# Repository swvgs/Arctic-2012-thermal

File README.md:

Arctic-2012-thermal
===================
This is Andrew Vaccaro's thermal processing script that was made to work with
raw data from Therma.

As of 5/2/13, these scripts are in a preliminary stage. They are only run from
the command line and require Python 2 to be installed. Later versions will
"hopefully" be stand-alone and have a GUI (assuming I ever get to them).

tim2.py takes original data files and splits them into multiple files, each one
containing the data along one survey line. tim2.py takes the data files and
processes them down to an equivalent number of data points between each survey
marker.

Currently, an unknown error prevents all of the code from being run in the same
file. Not entirely sure why, but splitting into two files works (thanks, CJ).
That being said, all file names and numbers are hard-coded into the scripts.
Annoying, but it's fairly simple to go in and edit the file name in tim2.py and
then the number of files produced in tim2.py.

tim3.py is in the works. It should be a single file that does the work of tim.py
and tim2.py. It is planned to account for error exceptions as well as gaps in or
issues with the data.

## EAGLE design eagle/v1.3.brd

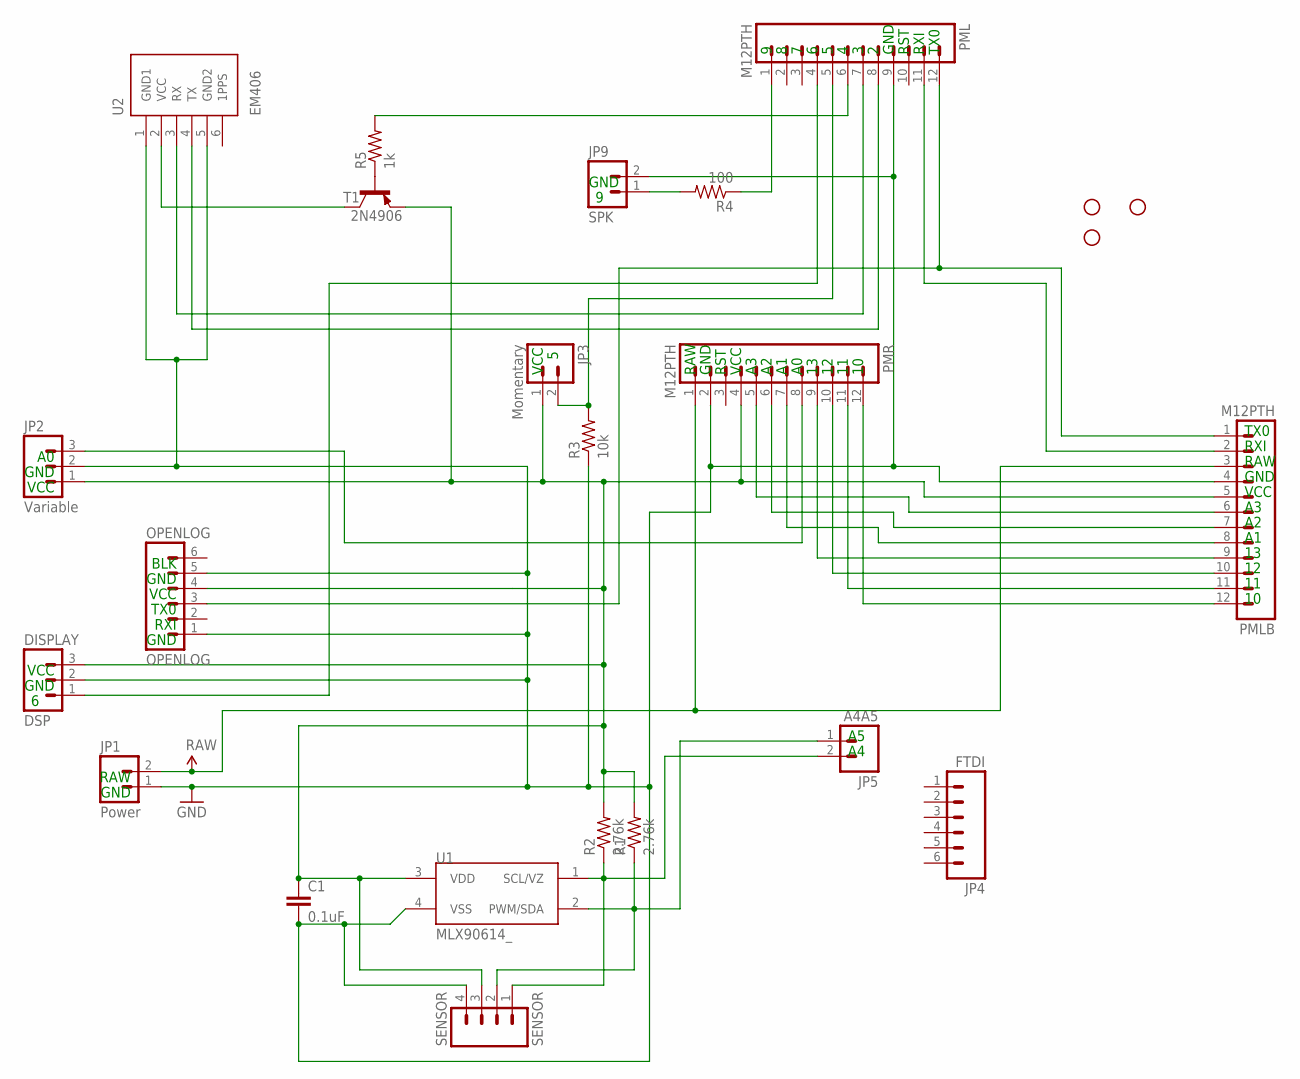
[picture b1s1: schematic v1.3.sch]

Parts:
2N4906: T1; TO92-EBC
C1: 0.1uF; CAP-PTH-LARGE
DISPLAY: DSP; SCREWTERMINAL-3.5MM-3_LOCK.007S
JP1: Power; JST-2-PTH
JP2: Variable; SCREWTERMINAL-3.5MM-3_LOCK.007S
JP3: Momentary; JST-2-PTH
JP4: FTDI; 1X06
JP5: A4A5; 1X02
JP6, JP7, JP8: STAND-OFFTIGHT; STAND-OFF-TIGHT
JP9: SPK; SCREWTERMINAL-3.5MM-2
OPENLOG: OPENLOG; 1X06_LOCK
PML: M12PTH; 1X12
PMLB: M12PTH; 1X12
PMR: M12PTH; 1X12
R1, R2: 2.76k; AXIAL-0.4
R3: 10k; AXIAL-0.4
R4: 100; AXIAL-0.4
R5: 1k; AXIAL-0.4
SENSOR: SENSOR; SCREWTERMINAL-3.5MM-4_LOCK
U1: MLX90614_; TO-39
U2: EM406

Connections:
GND: C1.2, DISPLAY.2, JP1.1, JP2.2, JP9.2, OPENLOG.1, OPENLOG.5, PML.9, PMLB.4, PMR.2, R3.P$1 (1), SENSOR.4, U1.4 (VSS), U2.1 (GND1), U2.5 (GND2)
unnamed: JP9.1, R4.P$2 (2)
unnamed: JP5.1, R1.P$1 (1), SENSOR.2, U1.2 (PWM/SDA)
unnamed: JP3.2, PML.5, R3.P$2 (2)
unnamed: DISPLAY.1, PML.4
unnamed: JP2.3, PMR.8
unnamed: OPENLOG.3, PML.12, PMLB.1
unnamed: PML.11, PMLB.2
unnamed: PMLB.12, PMR.12
unnamed: PMLB.11, PMR.11
unnamed: PMLB.10, PMR.10
unnamed: PMLB.9, PMR.9
unnamed: PMLB.8, PMR.7
unnamed: PMLB.7, PMR.6
unnamed: PMLB.6, PMR.5
unnamed: 2N4906.E, C1.1, DISPLAY.3, JP2.1, JP3.1, OPENLOG.4, PMLB.5, PMR.4, R1.P$2 (2), R2.P$2 (2), SENSOR.3, U1.3 (VDD)
unnamed: PML.1, R4.P$1 (1)
unnamed: 2N4906.B, R5.P$1 (1)
unnamed: 2N4906.C, U2.2 (VCC)
unnamed: PML.8, U2.4 (TX)
unnamed: PML.7, U2.3 (RX)
unnamed: PML.6, R5.P$2 (2)
SENSOR: JP5.2, R2.P$1 (1), SENSOR.1, U1.1 (SCL/VZ)
VCC: JP1.2, PMLB.3, PMR.1

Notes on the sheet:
RAW
GND
RST
VCC
TX0
RXI
BLK

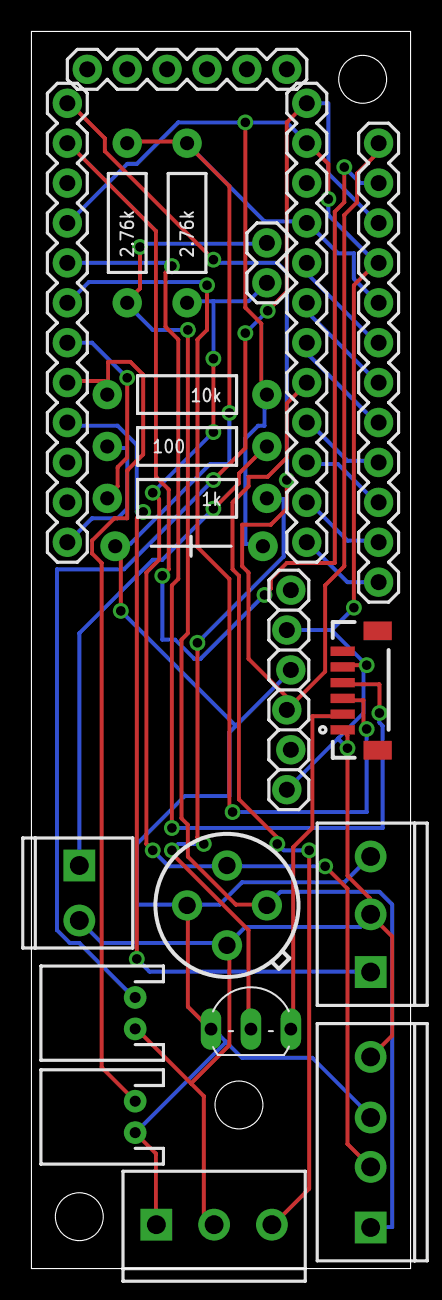
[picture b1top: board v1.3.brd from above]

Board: 2 copper layers, 24.1 x 78.7 mm, 24 parts (0 on the bottom side), 24 nets.

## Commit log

2013-05-01 Initial files
2013-06-25 Testing out git on the new laptop.
2013-07-07 this is the code used for the 2012 therma project.
2013-11-04 These are the eagle files for the 2012 board that was printed. v1.4b should be the final revision
